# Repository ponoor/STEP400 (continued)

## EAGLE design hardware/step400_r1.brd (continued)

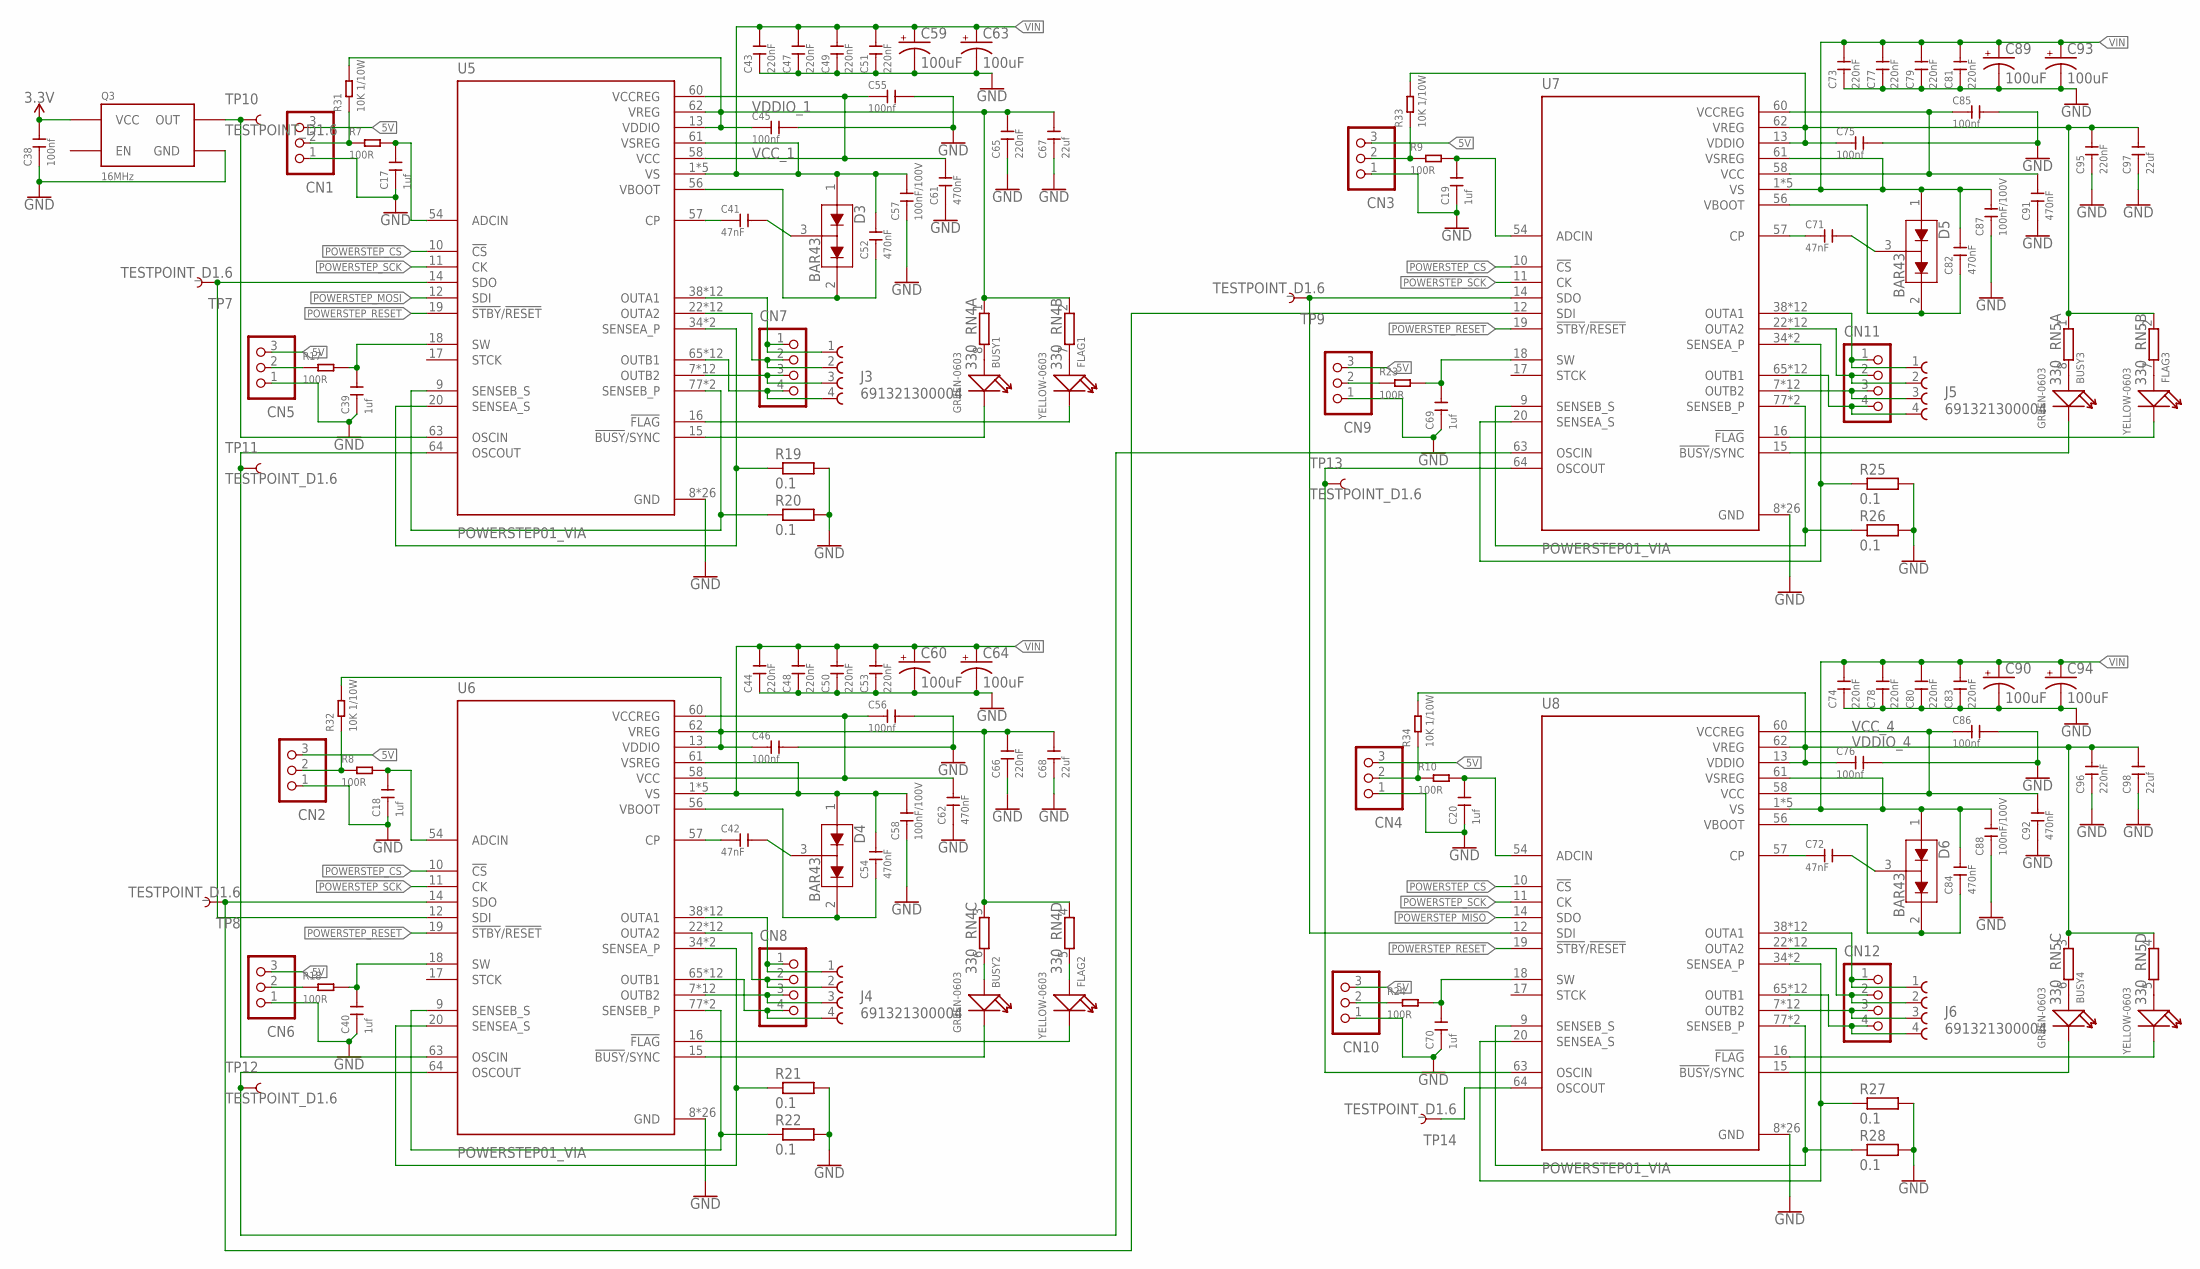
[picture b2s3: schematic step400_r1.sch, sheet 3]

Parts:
BUSY1, BUSY2, BUSY3, BUSY4: GREEN-0603; LED-0603
C17, C18, C19, C20, C39, C40, C69, C70: 1uf; C0603
C38, C45, C46, C55, C56, C75, C76, C85, C86: 100nf; C0402
C41, C42, C71, C72: 47nF; C0805
C43, C44, C47, C48, C49, C50, C51, C53, C73, C74, C77, C78, C79, C80, C81, C83: 220nF; C0805
C52, C54, C61, C62, C82, C84, C91, C92: 470nF; C0603
C57, C58, C87, C88: 100nF/100V; C0805
C59, C60, C63, C64, C89, C90, C93, C94: 100uF; E5-10,5
C65, C66, C95, C96: 220nF; C0402
C67, C68, C97, C98: 22uf; C0805
CN1, CN2, CN3, CN4, CN5, CN6, CN9, CN10: B3B-XASK-1
CN7, CN8, CN11, CN12: B4B-XASK-1
D3, D4, D5, D6: BAR43; SOT23-3
FLAG1, FLAG2, FLAG3, FLAG4: YELLOW-0603; LED-0603
J3, J4, J5, J6: 691321300004
Q3: 16MHz; SG5032
R7, R8, R9, R10, R17, R18, R23, R24: 100R; R0603
R19, R20, R21, R22, R25, R26, R27, R28: 0.1; RESC6332X71N
R31, R32, R33, R34: 10K 1/10W; R0603
RN4, RN5: 330; CAY16_LONG_W
TP7, TP8, TP9, TP10, TP11, TP12, TP13, TP14: TESTPOINT_D1.6
U5, U6, U7, U8: POWERSTEP01_VIA; IC_POWERSTEP01_VIA

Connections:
3.3V: C38.2, Q3.4 (VCC); also elsewhere on the board
5V: CN1.3, CN2.3, CN3.3, CN4.3, CN5.3, CN6.3, CN9.3, CN10.3; also elsewhere on the board
GND: C17.1, C18.1, C19.1, C20.1, C38.1, C39.1, C40.1, C43.1, C44.1, C45.2, C46.2, C47.1, C48.1, C49.1, C50.1, C51.1, C53.1, C55.2, C56.2, C57.1, C58.1, C59.-, C60.-, C61.1, C62.1, C63.-, C64.-, C65.1, C66.1, C67.1, C68.1, C69.1, C70.1, C73.1, C74.1, C75.2, C76.2, C77.1, C78.1, C79.1, C80.1, C81.1, C83.1, C85.2, C86.2, C87.1, C88.1, C89.-, C90.-, C91.1, C92.1, C93.-, C94.-, C95.1, C96.1, C97.1, C98.1, CN1.1, CN2.1, CN3.1, CN4.1, CN5.1, CN6.1, CN9.1, CN10.1, Q3.2 (GND), R19.2, R20.2, R21.2, R22.2, R25.2, R26.2, R27.2, R28.2, U5.8 (GND), U5.21 (GND), U5.59 (GND), U5.EPAD9 (GND), U5.EPAD9_VIA1 (GND), U5.EPAD9_VIA2 (GND), U5.EPAD9_VIA3 (GND), U5.EPAD9_VIA4 (GND), U5.EPAD9_VIA5 (GND), U5.EPAD9_VIA6 (GND), U5.EPAD9_VIA7 (GND), U5.EPAD9_VIA8 (GND), U5.EPAD9_VIA9 (GND), U5.EPAD9_VIA10 (GND), U5.EPAD9_VIA11 (GND), U5.EPAD9_VIA12 (GND), U5.EPAD9_VIA13 (GND), U5.EPAD9_VIA14 (GND), U5.EPAD9_VIA15 (GND), U5.EPAD9_VIA16 (GND), U5.EPAD9_VIA17 (GND), U5.EPAD9_VIA18 (GND), U5.EPAD9_VIA19 (GND), U5.EPAD9_VIA20 (GND), U5.EPAD9_VIA21 (GND), U5.EPAD9_VIA22 (GND), U6.8 (GND), U6.21 (GND), U6.59 (GND), U6.EPAD9 (GND), U6.EPAD9_VIA1 (GND), U6.EPAD9_VIA2 (GND), U6.EPAD9_VIA3 (GND), U6.EPAD9_VIA4 (GND), U6.EPAD9_VIA5 (GND), U6.EPAD9_VIA6 (GND), U6.EPAD9_VIA7 (GND), U6.EPAD9_VIA8 (GND), U6.EPAD9_VIA9 (GND), U6.EPAD9_VIA10 (GND), U6.EPAD9_VIA11 (GND), U6.EPAD9_VIA12 (GND), U6.EPAD9_VIA13 (GND), U6.EPAD9_VIA14 (GND), U6.EPAD9_VIA15 (GND), U6.EPAD9_VIA16 (GND), U6.EPAD9_VIA17 (GND), U6.EPAD9_VIA18 (GND), U6.EPAD9_VIA19 (GND), U6.EPAD9_VIA20 (GND), U6.EPAD9_VIA21 (GND), U6.EPAD9_VIA22 (GND), U7.8 (GND), U7.21 (GND), U7.59 (GND), U7.EPAD9 (GND), U7.EPAD9_VIA1 (GND), U7.EPAD9_VIA2 (GND), U7.EPAD9_VIA3 (GND), U7.EPAD9_VIA4 (GND), U7.EPAD9_VIA5 (GND), U7.EPAD9_VIA6 (GND), U7.EPAD9_VIA7 (GND), U7.EPAD9_VIA8 (GND), U7.EPAD9_VIA9 (GND), U7.EPAD9_VIA10 (GND), U7.EPAD9_VIA11 (GND), U7.EPAD9_VIA12 (GND), U7.EPAD9_VIA13 (GND), U7.EPAD9_VIA14 (GND), U7.EPAD9_VIA15 (GND), U7.EPAD9_VIA16 (GND), U7.EPAD9_VIA17 (GND), U7.EPAD9_VIA18 (GND), U7.EPAD9_VIA19 (GND), U7.EPAD9_VIA20 (GND), U7.EPAD9_VIA21 (GND), U7.EPAD9_VIA22 (GND), U8.8 (GND), U8.21 (GND), U8.59 (GND), U8.EPAD9 (GND), U8.EPAD9_VIA1 (GND), U8.EPAD9_VIA2 (GND), U8.EPAD9_VIA3 (GND), U8.EPAD9_VIA4 (GND), U8.EPAD9_VIA5 (GND), U8.EPAD9_VIA6 (GND), U8.EPAD9_VIA7 (GND), U8.EPAD9_VIA8 (GND), U8.EPAD9_VIA9 (GND), U8.EPAD9_VIA10 (GND), U8.EPAD9_VIA11 (GND), U8.EPAD9_VIA12 (GND), U8.EPAD9_VIA13 (GND), U8.EPAD9_VIA14 (GND), U8.EPAD9_VIA15 (GND), U8.EPAD9_VIA16 (GND), U8.EPAD9_VIA17 (GND), U8.EPAD9_VIA18 (GND), U8.EPAD9_VIA19 (GND), U8.EPAD9_VIA20 (GND), U8.EPAD9_VIA21 (GND), U8.EPAD9_VIA22 (GND); also elsewhere on the board
LIMIT1: C17.2, R7.2, U5.54 (ADCIN)
LIMIT2: C18.2, R8.2, U6.54 (ADCIN)
LIMIT3: C19.2, R9.2, U7.54 (ADCIN)
LIMIT4: C20.2, R10.2, U8.54 (ADCIN)
unnamed: TP14.1, U8.64 (OSCOUT)
unnamed: CN1.2, R7.1, R31.1
unnamed: CN2.2, R8.1, R32.1
unnamed: BUSY1.+, RN4.8 (2)
unnamed: CN5.2, R17.1
unnamed: C39.2, R17.2, U5.18 (SW)
unnamed: C40.2, R18.2, U6.18 (SW)
unnamed: CN6.2, R18.1
unnamed: C69.2, R23.2, U7.18 (SW)
unnamed: CN9.2, R23.1
unnamed: FLAG1.+, RN4.7 (2)
unnamed: C70.2, R24.2, U8.18 (SW)
unnamed: C41.2, D3.3 (COM)
unnamed: C41.1, U5.57 (CP)
unnamed: CN10.2, R24.1
unnamed: CN3.2, R9.1, R33.1
unnamed: BUSY2.+, RN4.6 (2)
unnamed: FLAG2.+, RN4.5 (2)
unnamed: FLAG1.-, U5.16 (!FLAG)
unnamed: BUSY1.-, U5.15 (!BUSY!/SYNC)
unnamed: R20.1, U5.9 (SENSEB_S), U5.77 (SENSEB_P), U5.82 (SENSEB_P)
unnamed: R19.1, U5.20 (SENSEA_S), U5.34 (SENSEA_P), U5.39 (SENSEA_P)
unnamed: CN4.2, R10.1, R34.1
unnamed: CN7.1, J3.1, U5.38 (OUTA1), U5.42 (OUTA1), U5.53 (OUTA1), U5.EPAD4 (OUTA1), U5.EPAD4_VIA1 (OUTA1), U5.EPAD4_VIA2 (OUTA1), U5.EPAD4_VIA3 (OUTA1), U5.EPAD4_VIA4 (OUTA1), U5.EPAD4_VIA5 (OUTA1), U5.EPAD4_VIA6 (OUTA1), U5.EPAD4_VIA7 (OUTA1), U5.EPAD4_VIA8 (OUTA1)
unnamed: CN7.2, J3.2, U5.22 (OUTA2), U5.33 (OUTA2), U5.37 (OUTA2), U5.EPAD3 (OUTA2), U5.EPAD3_VIA1 (OUTA2), U5.EPAD3_VIA2 (OUTA2), U5.EPAD3_VIA3 (OUTA2), U5.EPAD3_VIA4 (OUTA2), U5.EPAD3_VIA5 (OUTA2), U5.EPAD3_VIA6 (OUTA2), U5.EPAD3_VIA7 (OUTA2), U5.EPAD3_VIA8 (OUTA2)
unnamed: TP7.1, U5.14 (SDO), U6.12 (SDI)
unnamed: CN7.3, J3.3, U5.7 (OUTB2), U5.81 (OUTB2), U5.85 (OUTB2), U5.EPAD8 (OUTB2), U5.EPAD8_VIA1 (OUTB2), U5.EPAD8_VIA2 (OUTB2), U5.EPAD8_VIA3 (OUTB2), U5.EPAD8_VIA4 (OUTB2), U5.EPAD8_VIA5 (OUTB2), U5.EPAD8_VIA6 (OUTB2), U5.EPAD8_VIA7 (OUTB2), U5.EPAD8_VIA8 (OUTB2)
unnamed: CN7.4, J3.4, U5.65 (OUTB1), U5.76 (OUTB1), U5.80 (OUTB1), U5.EPAD7 (OUTB1), U5.EPAD7_VIA1 (OUTB1), U5.EPAD7_VIA2 (OUTB1), U5.EPAD7_VIA3 (OUTB1), U5.EPAD7_VIA4 (OUTB1), U5.EPAD7_VIA5 (OUTB1), U5.EPAD7_VIA6 (OUTB1), U5.EPAD7_VIA7 (OUTB1), U5.EPAD7_VIA8 (OUTB1)
unnamed: C42.2, D4.3 (COM)
unnamed: C42.1, U6.57 (CP)
unnamed: BUSY3.+, RN5.8 (2)
unnamed: FLAG3.+, RN5.7 (2)
unnamed: FLAG2.-, U6.16 (!FLAG)
unnamed: BUSY2.-, U6.15 (!BUSY!/SYNC)
unnamed: R22.1, U6.9 (SENSEB_S), U6.77 (SENSEB_P), U6.82 (SENSEB_P)
unnamed: R21.1, U6.20 (SENSEA_S), U6.34 (SENSEA_P), U6.39 (SENSEA_P)
unnamed: TP12.1, U6.64 (OSCOUT), U7.63 (OSCIN)
unnamed: CN8.1, J4.1, U6.38 (OUTA1), U6.42 (OUTA1), U6.53 (OUTA1), U6.EPAD4 (OUTA1), U6.EPAD4_VIA1 (OUTA1), U6.EPAD4_VIA2 (OUTA1), U6.EPAD4_VIA3 (OUTA1), U6.EPAD4_VIA4 (OUTA1), U6.EPAD4_VIA5 (OUTA1), U6.EPAD4_VIA6 (OUTA1), U6.EPAD4_VIA7 (OUTA1), U6.EPAD4_VIA8 (OUTA1)
unnamed: CN8.2, J4.2, U6.22 (OUTA2), U6.33 (OUTA2), U6.37 (OUTA2), U6.EPAD3 (OUTA2), U6.EPAD3_VIA1 (OUTA2), U6.EPAD3_VIA2 (OUTA2), U6.EPAD3_VIA3 (OUTA2), U6.EPAD3_VIA4 (OUTA2), U6.EPAD3_VIA5 (OUTA2), U6.EPAD3_VIA6 (OUTA2), U6.EPAD3_VIA7 (OUTA2), U6.EPAD3_VIA8 (OUTA2)
unnamed: CN8.3, J4.3, U6.7 (OUTB2), U6.81 (OUTB2), U6.85 (OUTB2), U6.EPAD8 (OUTB2), U6.EPAD8_VIA1 (OUTB2), U6.EPAD8_VIA2 (OUTB2), U6.EPAD8_VIA3 (OUTB2), U6.EPAD8_VIA4 (OUTB2), U6.EPAD8_VIA5 (OUTB2), U6.EPAD8_VIA6 (OUTB2), U6.EPAD8_VIA7 (OUTB2), U6.EPAD8_VIA8 (OUTB2)
unnamed: CN8.4, J4.4, U6.65 (OUTB1), U6.76 (OUTB1), U6.80 (OUTB1), U6.EPAD7 (OUTB1), U6.EPAD7_VIA1 (OUTB1), U6.EPAD7_VIA2 (OUTB1), U6.EPAD7_VIA3 (OUTB1), U6.EPAD7_VIA4 (OUTB1), U6.EPAD7_VIA5 (OUTB1), U6.EPAD7_VIA6 (OUTB1), U6.EPAD7_VIA7 (OUTB1), U6.EPAD7_VIA8 (OUTB1)
unnamed: BUSY4.+, RN5.6 (2)
unnamed: C82.1, D5.2 (C2), U7.56 (VBOOT)
unnamed: C71.2, D5.3 (COM)
unnamed: C71.1, U7.57 (CP)
unnamed: FLAG4.+, RN5.5 (2)
unnamed: CN11.4, J5.4, U7.65 (OUTB1), U7.76 (OUTB1), U7.80 (OUTB1), U7.EPAD7 (OUTB1), U7.EPAD7_VIA1 (OUTB1), U7.EPAD7_VIA2 (OUTB1), U7.EPAD7_VIA3 (OUTB1), U7.EPAD7_VIA4 (OUTB1), U7.EPAD7_VIA5 (OUTB1), U7.EPAD7_VIA6 (OUTB1), U7.EPAD7_VIA7 (OUTB1), U7.EPAD7_VIA8 (OUTB1)
unnamed: FLAG3.-, U7.16 (!FLAG)
unnamed: BUSY3.-, U7.15 (!BUSY!/SYNC)
unnamed: R26.1, U7.9 (SENSEB_S), U7.77 (SENSEB_P), U7.82 (SENSEB_P)
unnamed: R25.1, U7.20 (SENSEA_S), U7.34 (SENSEA_P), U7.39 (SENSEA_P)
unnamed: TP8.1, U6.14 (SDO), U7.12 (SDI)
unnamed: CN11.1, J5.1, U7.38 (OUTA1), U7.42 (OUTA1), U7.53 (OUTA1), U7.EPAD4 (OUTA1), U7.EPAD4_VIA1 (OUTA1), U7.EPAD4_VIA2 (OUTA1), U7.EPAD4_VIA3 (OUTA1), U7.EPAD4_VIA4 (OUTA1), U7.EPAD4_VIA5 (OUTA1), U7.EPAD4_VIA6 (OUTA1), U7.EPAD4_VIA7 (OUTA1), U7.EPAD4_VIA8 (OUTA1)
unnamed: CN11.2, J5.2, U7.22 (OUTA2), U7.33 (OUTA2), U7.37 (OUTA2), U7.EPAD3 (OUTA2), U7.EPAD3_VIA1 (OUTA2), U7.EPAD3_VIA2 (OUTA2), U7.EPAD3_VIA3 (OUTA2), U7.EPAD3_VIA4 (OUTA2), U7.EPAD3_VIA5 (OUTA2), U7.EPAD3_VIA6 (OUTA2), U7.EPAD3_VIA7 (OUTA2), U7.EPAD3_VIA8 (OUTA2)
unnamed: CN11.3, J5.3, U7.7 (OUTB2), U7.81 (OUTB2), U7.85 (OUTB2), U7.EPAD8 (OUTB2), U7.EPAD8_VIA1 (OUTB2), U7.EPAD8_VIA2 (OUTB2), U7.EPAD8_VIA3 (OUTB2), U7.EPAD8_VIA4 (OUTB2), U7.EPAD8_VIA5 (OUTB2), U7.EPAD8_VIA6 (OUTB2), U7.EPAD8_VIA7 (OUTB2), U7.EPAD8_VIA8 (OUTB2)
unnamed: CN12.4, J6.4, U8.65 (OUTB1), U8.76 (OUTB1), U8.80 (OUTB1), U8.EPAD7 (OUTB1), U8.EPAD7_VIA1 (OUTB1), U8.EPAD7_VIA2 (OUTB1), U8.EPAD7_VIA3 (OUTB1), U8.EPAD7_VIA4 (OUTB1), U8.EPAD7_VIA5 (OUTB1), U8.EPAD7_VIA6 (OUTB1), U8.EPAD7_VIA7 (OUTB1), U8.EPAD7_VIA8 (OUTB1)
unnamed: CN12.3, J6.3, U8.7 (OUTB2), U8.81 (OUTB2), U8.85 (OUTB2), U8.EPAD8 (OUTB2), U8.EPAD8_VIA1 (OUTB2), U8.EPAD8_VIA2 (OUTB2), U8.EPAD8_VIA3 (OUTB2), U8.EPAD8_VIA4 (OUTB2), U8.EPAD8_VIA5 (OUTB2), U8.EPAD8_VIA6 (OUTB2), U8.EPAD8_VIA7 (OUTB2), U8.EPAD8_VIA8 (OUTB2)
unnamed: C84.1, D6.2 (C2), U8.56 (VBOOT)
unnamed: C72.2, D6.3 (COM)
unnamed: C72.1, U8.57 (CP)
unnamed: FLAG4.-, U8.16 (!FLAG)
unnamed: BUSY4.-, U8.15 (!BUSY!/SYNC)
unnamed: R28.1, U8.9 (SENSEB_S), U8.77 (SENSEB_P), U8.82 (SENSEB_P)
unnamed: R27.1, U8.20 (SENSEA_S), U8.34 (SENSEA_P), U8.39 (SENSEA_P)
unnamed: CN12.1, J6.1, U8.38 (OUTA1), U8.42 (OUTA1), U8.53 (OUTA1), U8.EPAD4 (OUTA1), U8.EPAD4_VIA1 (OUTA1), U8.EPAD4_VIA2 (OUTA1), U8.EPAD4_VIA3 (OUTA1), U8.EPAD4_VIA4 (OUTA1), U8.EPAD4_VIA5 (OUTA1), U8.EPAD4_VIA6 (OUTA1), U8.EPAD4_VIA7 (OUTA1), U8.EPAD4_VIA8 (OUTA1)
unnamed: CN12.2, J6.2, U8.22 (OUTA2), U8.33 (OUTA2), U8.37 (OUTA2), U8.EPAD3 (OUTA2), U8.EPAD3_VIA1 (OUTA2), U8.EPAD3_VIA2 (OUTA2), U8.EPAD3_VIA3 (OUTA2), U8.EPAD3_VIA4 (OUTA2), U8.EPAD3_VIA5 (OUTA2), U8.EPAD3_VIA6 (OUTA2), U8.EPAD3_VIA7 (OUTA2), U8.EPAD3_VIA8 (OUTA2)
unnamed: Q3.3 (OUT), TP10.1, U5.63 (OSCIN)
unnamed: TP11.1, U5.64 (OSCOUT), U6.63 (OSCIN)
unnamed: TP13.1, U7.64 (OSCOUT), U8.63 (OSCIN)
unnamed: TP9.1, U7.14 (SDO), U8.12 (SDI)
POWERSTEP_CS: U5.10 (!CS), U6.10 (!CS), U7.10 (!CS), U8.10 (!CS); also elsewhere on the board
POWERSTEP_MISO: U8.14 (SDO); also elsewhere on the board
POWERSTEP_MOSI: U5.12 (SDI); also elsewhere on the board
POWERSTEP_RESET: U5.19 (!STBY!/!RESET), U6.19 (!STBY!/!RESET), U7.19 (!STBY!/!RESET), U8.19 (!STBY!/!RESET); also elsewhere on the board
POWERSTEP_SCK: U5.11 (CK), U6.11 (CK), U7.11 (CK), U8.11 (CK); also elsewhere on the board
VBOOT_1: C52.1, D3.2 (C2), U5.56 (VBOOT)
VBOOT_2: C54.1, D4.2 (C2), U6.56 (VBOOT)
VCC_1: C55.1, C61.2, U5.58 (VCC), U5.60 (VCCREG)
VCC_2: C56.1, C62.2, U6.58 (VCC), U6.60 (VCCREG)
VCC_3: C85.1, C91.2, U7.58 (VCC), U7.60 (VCCREG)
VCC_4: C86.1, C92.2, U8.58 (VCC), U8.60 (VCCREG)
VDDIO_1: C45.1, C65.2, C67.2, R31.2, RN4.1, RN4.2 (1), U5.13 (VDDIO), U5.62 (VREG)
VDDIO_2: C46.1, C66.2, C68.2, R32.2, RN4.3 (1), RN4.4 (1), U6.13 (VDDIO), U6.62 (VREG)
VDDIO_3: C75.1, C95.2, C97.2, R33.2, RN5.1, RN5.2 (1), U7.13 (VDDIO), U7.62 (VREG)
VDDIO_4: C76.1, C96.2, C98.2, R34.2, RN5.3 (1), RN5.4 (1), U8.13 (VDDIO), U8.62 (VREG)
VIN: C43.2, C44.2, C47.2, C48.2, C49.2, C50.2, C51.2, C52.2, C53.2, C54.2, C57.2, C58.2, C59.+, C60.+, C63.+, C64.+, C73.2, C74.2, C77.2, C78.2, C79.2, C80.2, C81.2, C82.2, C83.2, C84.2, C87.2, C88.2, C89.+, C90.+, C93.+, C94.+, D3.1 (A1), D4.1 (A1), D5.1 (A1), D6.1 (A1), U5.1 (VS), U5.23 (VS), U5.43 (VS), U5.55 (VS), U5.61 (VSREG), U5.66 (VS), U6.1 (VS), U6.23 (VS), U6.43 (VS), U6.55 (VS), U6.61 (VSREG), U6.66 (VS), U7.1 (VS), U7.23 (VS), U7.43 (VS), U7.55 (VS), U7.61 (VSREG), U7.66 (VS), U8.1 (VS), U8.23 (VS), U8.43 (VS), U8.55 (VS), U8.61 (VSREG), U8.66 (VS); also elsewhere on the board

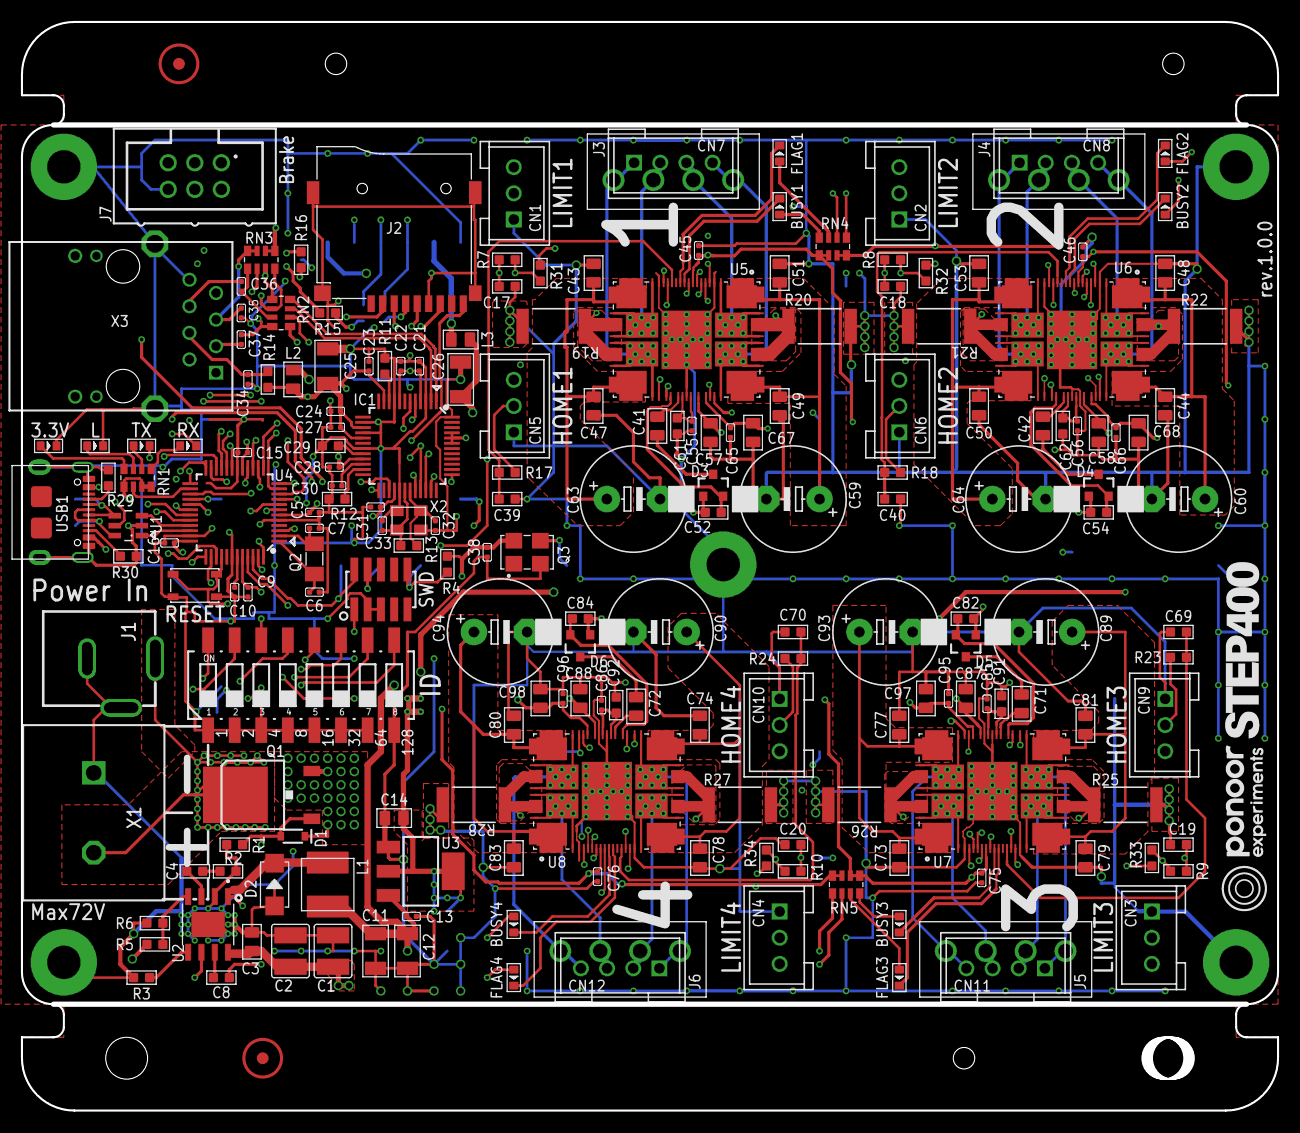
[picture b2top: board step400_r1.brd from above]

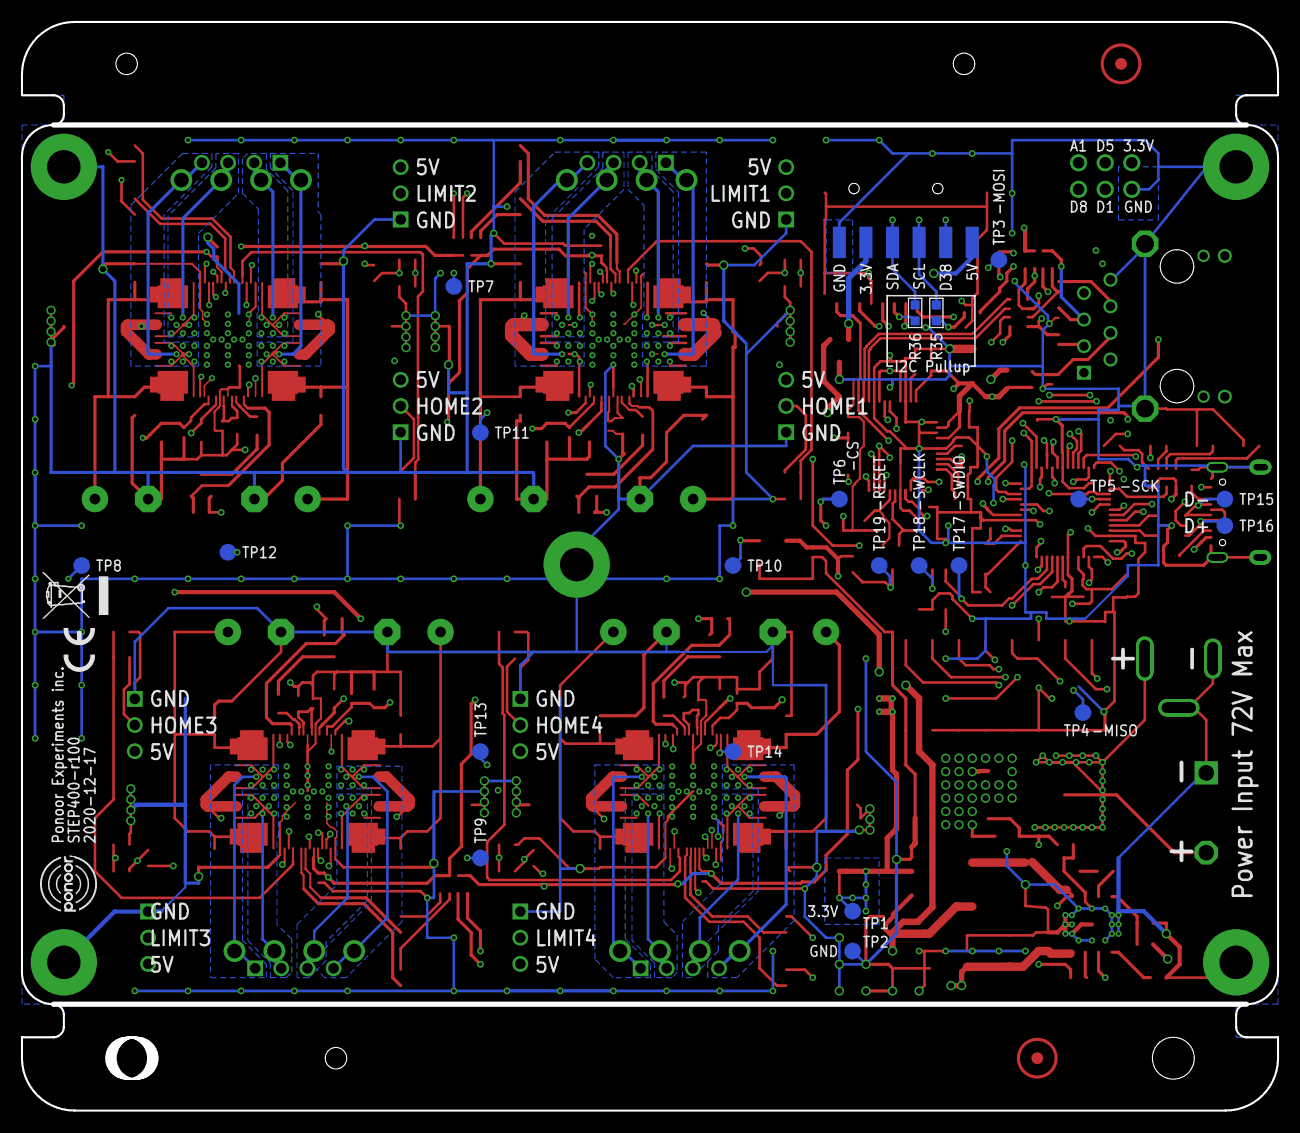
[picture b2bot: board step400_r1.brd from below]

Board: 4 copper layers, 120.0 x 104.0 mm, 229 parts (25 on the bottom side), 166 nets.

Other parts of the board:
U$1: STEP400_LOGO_6MM
U$2, U$3: FIDUCIAL_MARKER_PBAN
U$4: PONOOR_LOGO_6MM
U$6: WEEE_6MM
U$8: CE_3MM

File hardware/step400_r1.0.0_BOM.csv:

#,Name,Value,Description,Package,Manufacture,Manufacturer Part Number,Designator,Qty,Type,
1,SMD-LED,GREEN,general LED green,LED-0603,Lite-On,LTST-C193TGKT-5A,"3.3V, BUSY1, BUSY2, BUSY3, BUSY4",5,SMD,
2,MLCC,4.7uF/100V,4.7uF / 20% / 100V / X5R,C1210,Samsung Electro-Mechanics,CL32B475KCVZW6E,"C1, C2",2,SMD,
3,MLCC,47uF/6.3V,47uF / 20% / 6.3V / X5R,C1206,Samsung Electro-Mechanics,CL31A476MQHNNWE,"C11, C12, C25, C26",4,SMD,
4,MLCC,10uF/10V,10uF / 20% / 10V / X5R,C0805,Samsung Electro-Mechanics,CL21A106KOQNNNG,C14,1,SMD,
5,MLCC,1uF/6.3V,1uF / 20% / 6.3V / X5R,C0603,Samsung Electro-Mechanics,CL10A105KO8NNNC,"C17, C18, C19, C20, C39, C40, C69, C70",8,SMD,
6,MLCC,4.7uF/6.3V,4.7uF / 20% / 6.3V / X5R,C0603,Samsung Electro-Mechanics,CL10A475KQ8NNNC,C29,1,SMD,
7,MLCC,100nF/100V,100nF / 20% / 100V / X5R,C0805,Samsung Electro-Mechanics,CL21B104KCFNNNE,"C3, C57, C58, C87, C88",5,SMD,
8,MLCC,10nF/25V,10nF / 20% / 25V / X5R ,C0402,Walsin Tech Corp,0402B103K250,"C30, C35",2,SMD,
9,MLCC,22nF 50V,22nF / 20% / 50V / X5R,C0402,Walsin Tech Corp,0402F223Z500CT,C34,1,SMD,
10,MLCC,6.8nF/25V,6.8nF / 20% / 25V / X5R ,C0402,Walsin Tech Corp,0402B682K500CT,"C36, C37",2,SMD,
11,MLCC,100nF/50V,100nF / 20% / 50V / X5R,C0603,Walsin Tech Corp,0603B104K500CT,"C4, C8",2,SMD,
12,MLCC,47nF/50V,47nF / 20% / 50V / X5R,C0805,Samsung Electro-Mechanics,CL21F473ZBANNNC,"C41, C42, C71, C72",4,SMD,
13,MLCC,220nF/100V,220nF / 20% / 100V / X5R,C0805,Samsung Electro-Mechanics,CL21B224KCFSFNE,"C43, C44, C47, C48, C49, C50, C51, C53, C73, C74, C77, C78, C79, C80, C81, C83",16,SMD,
14,MLCC,100nF / 25V,100nF / 20% / 25V / X5R,C0402,Walsin Tech Corp,0402X104K160CT,"C5, C9, C10, C13, C15, C16, C21, C22, C23, C24, C27, C28, C31, C38, C45, C46, C55, C56, C75, C76, C85, C86",22,SMD,
15,MLCC,470nF/25V,470nF / 20% / 25V / X5R ,C0603,Samsung Electro-Mechanics,CL10B474KA8NNNC,"C52, C54, C61, C62, C82, C84, C91, C92",8,SMD,
16,Chemical Capacitor,100uF/100V,100uF / 20% / 100V,"E5-10,5",Rubycon,100PX100MEFC10X16,"C59, C60, C63, C64, C89, C90, C93, C94",8,THT,
17,MLCC,22pF/50V,22pF / 10% / 50V / X5R,C0402,Walsin Tech Corp,0402N220J500,"C6, C7, C32, C33",4,SMD,
18,MLCC,220nF/6.3V,220nF / 20% / 6.3V / X5R,C0402,Walsin Tech Corp,0402X224K6R3CT,"C65, C66, C95, C96",4,SMD,
19,MLCC,22uF/6.3V,22uF / 20% / 6.3V / X5R,C0805,Samsung Electro-Mechanics,CL21A226MQQNNNE,"C67, C68, C97, C98",4,SMD,
20,Shrouded header,"2.5mm, 3P",B3B-XASK-1,B3B-XASK-1,JST,B03B-XASK-1(LF)(SN),"CN1, CN2, CN3, CN4, CN5, CN6, CN9, CN10",8,THT,
21,Shrouded header,"2.5mm, 4P",B4B-XASK-1,B4B-XASK-1,JST,B04B-XASK-1(LF)(SN),"CN7, CN8, CN11, CN12",4,THT,NO mount
22,Zener Diode,"5.6V, 300mW",5.6V ±7% 300mW ,SOD-323,ON Semiconductor,MM3Z5V6T1G,D1,1,SMD,
23,Schottky diode,100V 2A,"100V, 2A",DO-214AC,Guangdong Hottech,SS210A,D2,1,SMD,
24,Switching diode array,BAR43,"30V, 100mA",SOT23-3,STMicroelectronics,BAR43SFILM,"D3, D4, D5, D6",4,SMD,
25,SMD-LED,Red,general LED red,LED-0603,Lite-On,LTST-C193KRKT-5A,"FLAG1, FLAG2, FLAG3, FLAG4, TX",5,SMD,
26,Ethernet Controller,,,TQFP48,WIZnet,W5500,IC1,1,SMD,
27,DIP Switch,,8 digits,2.54mm pitch SMD,Cixi Tonver Elec,HAD-08HWA-R,ID,1,SMD,
28,DC Power receptacle,,DC Power Receptacle Jack 5A 2.0mm 6.2mm,POWERJACK_SLOT,XKB Connectivity,DC-005-5A-2.0,J1,1,SMD,
29,Micro SD card slot,,,,XUNPU,TF-115K,J2,1,SMD,
30,3.81mm 4pin header,,,,Ningbo Kangnex Elec,WJ15EDGVC-3.81-4P,"J3, J4, J5, J6",4,THT,
31,Box header,,"Header 6P 0.100""(2.54mm) 2",61200621621,Ckmtw(Shenzhen Cankemeng),C132438,J7,1,THT,
32,SMD-LED,Orange,general LED orange,LED-0603,Lite-On,LTST-C191KFKT,L,1,SMD,
33,Power Inductor,15uH,±20% 1.9A,L5050,TDK,VLS5045EX-150M,L1,1,SMD,
34,Ferrite Beads,330R-1500MA,330Ω @ 100MHz 1.5A,L0805,Murata Electronics,"BLM21PG331SN1D","L2, L3",2,SMD,
35,P-MOSFET,,100V 46A,D-PAK(TO252AA),Winsok Semicon,WSF45P10,Q1,1,SMD,
36,Crystal Resonators,32.768kHz,CRYSTAL,SMD-3215_2P,EPSON,FC-135 32.7680KA-A0,Q2,1,SMD,
37,Crystal Oscillator,,16MHz ±100ppm 3.3V,SG5032,Seiko Epson,X1G004451000200,Q3,1,SMD,
38,Chip Resistor,100k,5% 1/10W,R0603,YAGEO,RC0603JR-07100KL,R1,1,SMD,
39,Chip Resistor,12.4K,1％ 1/10W,R0603,YAGEO,AC0603FR-0712K4L,R11,1,SMD,
40,Chip Resistor,1M 1/10W,5% 1/10W,R0603,YAGEO,AC0603JR-071ML,R13,1,SMD,
41,Chip Resistor,10R,5% 1/10W,R0603,YAGEO,RC0603JR-0710RL,R14,1,SMD,
42,Chip Resistor,330R,5% 1/10W,R0603,YAGEO,RC0603JR-07330RL,"R15, R16",2,SMD,
43,Chip Resistor,0.1,1% 3W,R2512,Bourns,CRA2512-FZ-R100ELF,"R19, R20, R21, R22, R25, R26, R27, R28",8,SMD,
44,Chip Resistor,4.7k,5% 1/10W,R0603,YAGEO,AC0603JR-074K7L,R2,1,SMD,
45,Chip Resistor,5.1k,±0.5% 0.1W,R0603,YAGEO,RC0603DR-075K1L,"R29, R30",2,SMD,
46,Chip Resistor,13k,1％ 1/10W,R0603,YAGEO,RC0603FR-0713KL,R3,1,SMD,
47,Chip Resistor,10K 1/10W,5% 1/10W,R0603,YAGEO,RC0603JR-0710KL,"R4, R12, R31, R32, R33, R34",6,SMD,
48,Chip Resistor,3k,1％ 1/10W,R0603,YAGEO,RC0603FR-073KL,R5,1,SMD,
49,Chip Resistor,750,1％ 1/10W,R0603,YAGEO,AC0603DR-07750RL,R6,1,SMD,
50,Chip Resistor,100R,5% 1/10W,R0603,YAGEO,RC0603JR-07100RL,"R7, R8, R9, R10, R17, R18, R23, R24",8,SMD,
51,Tactile Switch,,SWITCH-SPST,4.6x3.2,ALPS Electric,SKRPABE010,RESET,1,SMD,
52,Array Chip Resistor,330,5% 1/16W,R0603 x4,Bourns,CAY16-331J4LF,"RN1, RN4, RN5",3,SMD,
53,Array Chip Resistor,33,5% 1/16W,R0603 x4,Bourns,CAY16-330J4LF,RN2,1,SMD,
54,Array Chip Resistor,49.9,1% 1/16W,R0603 x4,Bourns,CAY16-49R9F4LF,RN3,1,SMD,
55,SMD-LED,Yellow,general LED yellow,LED-0603,Lite-On,LTST-C191KSKT,RX,1,SMD,
56,Pin Header,10 pin,Cortex Debug Connector,1.27mm Pin Header 10P,Amphenol ICC,20021121-00010C4LF,SWD,1,SMD,
57,TVS Diode Array,USBLC6-2SC6,STMicroelectronics  USBLC6,SOT23-6L,STMicroelectronics,USBLC6-2SC6,U1,1,SMD,
58,DC-DC converter,,,HTSOP-J8,ROHM,BD9G341AEFJ-E2,U2,1,SMD,
59,Voltage Regulator,LD1117S33,3.3V 0.8A,SOT223,STMicroelectronics,LD1117S33TR,U3,1,SMD,
60,MCU,,,TQFP-48,Microchip,ATSAMD21G18A-AU,U4,1,SMD,
61,Stepper Motor Driver,,,VFQFPN89,STMicroelectronics,POWERSTEP01TR,"U5, U6, U7, U8",4,SMD,
62,USB Type C Connector,,USB - Type C Female 16 SMT,USB-C_USB2.0-TYPE-C,XKB Connectivity,U262-161N-4BVC11,USB1,1,THT,
63,Barrier Terminal Block,"7.62mm, 2P",,7.62mm,Ningbo Kangnex Elec,WJ25C-B-7.62-2P,X1,1,SMD,
64,Crystal Resonators ,25MHz,25MHz ±20ppm12pF,CRYSTAL-3225,Seiko Epson,X1E000021013900,X2,1,SMD,
65,RJ45 Jack with Magnetics,,,,Hanrun,HR871181A,X3,1,THT,

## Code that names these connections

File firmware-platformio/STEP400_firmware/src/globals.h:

// globals.h

#ifndef _GLOBALS_h
#define _GLOBALS_h

#if defined(ARDUINO) && ARDUINO >= 100
	#include "arduino.h"
#else
	#include "WProgram.h"
#endif
#include <SPI.h>
#include <Ponoor_PowerSTEP01Library.h>
#include <Ethernet.h>

//#define PROTOTYPE_R4 // Uncomment this line for the prototype r4 pcb.

// =============================================================================
// Pin definitions
// =============================================================================
#define ledPin	13u

#ifdef PROTOTYPE_R4
const uint8_t dipSwPin[8] = { A5,SCL,7u,SDA,2u,9u,3u,0u }; // Prototype_r4
const uint8_t limitSwPin[4] = { 1u,5u,8u,A1 };
#else
const uint8_t dipSwPin[8] = { 7u,30u,A5,31u,2u,9u,3u,0u };
#endif

#define SD_CS_PIN	4u

const uint8_t brakePin[4] = { A1,8u,5u,1u };
#define SD_DETECT_PIN   A4

#define POWERSTEP_MISO	6u	// D6 /SERCOM3/PAD[2] miso
#define POWERSTEP_MOSI	11u	// D11/SERCOM3/PAD[0] mosi
#define POWERSTEP_SCK	12u	// D12/SERCOM3/PAD[3] sck
#define POWERSTEP_CS_PIN A0
#define POWERSTEP_RESET_PIN A2

#define W5500_RESET_PIN A3

// =============================================================================
// Constants and variables
// =============================================================================

// General
#define COMPILE_DATE __DATE__
#define COMPILE_TIME __TIME__
extern const char *firmwareName;
extern const uint8_t firmwareVersion[3]; // defined in the main Arduino sketch
extern int8_t loadedConfigVersion[2];
extern const uint8_t applicableConfigVersion[2];
#define STATUS_POLL_PERIOD   1 // [ms]


// Tx, Rx LED
extern bool rxLedEnabled, txLedEnabled;
extern uint32_t RXL_blinkStartTime, TXL_blinkStartTime;
#define RXL_TXL_BLINK_DURATION	30 // ms

// Json configuration file
constexpr char* filename = "/config.txt";
extern String configName;
extern String configTargetProduct;
extern bool sdInitializeSucceeded;
extern bool configFileOpenSucceeded;
extern bool configFileParseSucceeded;

// PowerSTEP01
#define NUM_OF_MOTOR   (4)
extern powerSTEP stepper[];
#define MOTOR_ID_ALL    255
#define MOTOR_ID_FIRST  1
#define MOTOR_ID_LAST   4

// Network
extern uint8_t mac[6], mac_from_config[6], myId;
extern IPAddress
    myIp,
    myIp_from_config,
    destIp,
    dns,
    gateway,
    subnet;
const IPAddress broadcastIp(255, 255, 255, 255);
extern unsigned int inPort, outPort, outPort_from_config;
extern EthernetUDP Udp;
extern bool
    isDestIpSet,
    isMyIpAddId,
    isMacAddId,
    isOutPortAddId,
    bootedMsgEnable,
    isWaitingSendBootMsg,
    reportErrors;
#define BOOT_MSG_WAIT_TIME  1000    //[ms], The waiting duration for sending a boot message after Ethernet has been linked

// Motor settings.
#define TVAL_LIMIT_VAL  64 // approx. 5A

// Brake
extern uint8_t brakeStatus[NUM_OF_MOTOR];
enum {
    BRAKE_ENGAGED = 0,
    BRAKE_DISENGAGE_WAITING, // motor excited
    BRAKE_DISENGAGED,
    BRAKE_MOTORHIZ_WAITING // brake closed
};
extern uint32_t brakeTransitionTrigTime[NUM_OF_MOTOR];
extern bool bBrakeDecWaiting[NUM_OF_MOTOR]; // Waiting deceleration for the brake engaging procedure

// Homing
extern uint32_t homingStartTime[NUM_OF_MOTOR];
extern uint8_t homingStatus[NUM_OF_MOTOR];
extern bool bHoming[NUM_OF_MOTOR];
extern float homingSpeed[NUM_OF_MOTOR];
enum {
    HOMING_UNDEFINED = 0,
    HOMING_GOUNTIL,
    HOMING_RELEASESW,
    HOMING_COMPLETED,
    HOMING_TIMEOUT
};

// Command errors
enum {
    ERROR_COMMAND_IGNORED = 0,
    ERROR_MOTORID_NOTMATCH,
    ERROR_BRAKE_ENGAGED,
    ERROR_HOMESW_ACTIVATING,
    ERROR_LIMITSW_ACTIVATING,
    ERROR_GOUNTIL_TIMEOUT,
    ERROR_RELEASESW_TIMEOUT,
    ERROR_IN_SERVO_MODE
};
const String commandErrorText[8] = {
    F("CommandIgnored"),
    F("MotorIdNotMatch"),
    F("BrakeEngaged"),
    F("HomeSwActivating"),
    F("LimitSwActivating"),
    F("GoUntilTimeout"),
    F("ReleaseSwTimeout"),
    F("InServoMode")
};
// These values will be initialized at loadConfig()
extern bool
    busy[NUM_OF_MOTOR],
    HiZ[NUM_OF_MOTOR],
    homeSwState[NUM_OF_MOTOR],
    dir[NUM_OF_MOTOR],
    uvloStatus[NUM_OF_MOTOR];
extern uint8_t
    motorStatus[NUM_OF_MOTOR],
    thermalStatus[NUM_OF_MOTOR];

extern bool
    reportBUSY[NUM_OF_MOTOR],
    reportHiZ[NUM_OF_MOTOR],
    reportHomeSwStatus[NUM_OF_MOTOR],
    reportDir[NUM_OF_MOTOR],
    reportMotorStatus[NUM_OF_MOTOR],
    reportSwEvn[NUM_OF_MOTOR],
    reportUVLO[NUM_OF_MOTOR],
    reportThermalStatus[NUM_OF_MOTOR],
    reportOCD[NUM_OF_MOTOR],
    reportStall[NUM_OF_MOTOR],
    limitSwState[NUM_OF_MOTOR],
    reportLimitSwStatus[NUM_OF_MOTOR],
    limitSwMode[NUM_OF_MOTOR],
    homingDirection[NUM_OF_MOTOR],
    bProhibitMotionOnHomeSw[NUM_OF_MOTOR],
    bProhibitMotionOnLimitSw[NUM_OF_MOTOR],
    bHomingAtStartup[NUM_OF_MOTOR];
extern uint16_t
    goUntilTimeout[NUM_OF_MOTOR],
    releaseSwTimeout[NUM_OF_MOTOR];
extern uint8_t kvalHold[NUM_OF_MOTOR], kvalRun[NUM_OF_MOTOR], kvalAcc[NUM_OF_MOTOR], kvalDec[NUM_OF_MOTOR];
extern uint8_t tvalHold[NUM_OF_MOTOR], tvalRun[NUM_OF_MOTOR], tvalAcc[NUM_OF_MOTOR], tvalDec[NUM_OF_MOTOR];
extern bool isCurrentMode[NUM_OF_MOTOR];
extern bool homeSwMode[NUM_OF_MOTOR];

extern uint16_t intersectSpeed[NUM_OF_MOTOR]; // INT_SPEED
extern uint8_t
    startSlope[NUM_OF_MOTOR], // ST_SLP
    accFinalSlope[NUM_OF_MOTOR], // FN_SLP_ACC
    decFinalSlope[NUM_OF_MOTOR], // FN_SLP_DEC
    stallThreshold[NUM_OF_MOTOR]; // STALL_TH
extern uint8_t
    fastDecaySetting[NUM_OF_MOTOR], // T_FAST
    minOnTime[NUM_OF_MOTOR], // TON_MIN
    minOffTime[NUM_OF_MOTOR]; // TOFF_MIN
extern uint8_t
    overCurrentThreshold[NUM_OF_MOTOR], // OCD
    microStepMode[NUM_OF_MOTOR]; // STEP_MODE
extern uint16_t slewRate[NUM_OF_MOTOR]; // GATECFG1
extern uint8_t slewRateNum[NUM_OF_MOTOR]; // [0]114, [1]220, [2]400, [3]520, [4]790, [5]980.
extern float lowSpeedOptimize[NUM_OF_MOTOR];
extern bool electromagnetBrakeEnable[NUM_OF_MOTOR];
extern uint16_t brakeTransitionDuration[NUM_OF_MOTOR];
extern float
    acc[NUM_OF_MOTOR],
    dec[NUM_OF_MOTOR],
    maxSpeed[NUM_OF_MOTOR],
    fullStepSpeed[NUM_OF_MOTOR];

// Servo mode
extern int32_t targetPosition[NUM_OF_MOTOR];
extern float kP[NUM_OF_MOTOR], kI[NUM_OF_MOTOR], kD[NUM_OF_MOTOR];
extern boolean isServoMode[NUM_OF_MOTOR];
#endif

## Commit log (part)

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2020-12-18 Added hardware design files.
2020-12-18 updated .gitignore
2020-12-20 Added BOM lists
2021-01-23 Added a hardware inspection sketch
2021-01-25 Added config tool files
2021-01-26 Convert multiple .ino files style to .h .cpp style
2021-01-27 Added the PlatformIO working folder
2021-02-15 update osc float/int compatibility for each commands
2021-02-17 electromagnet brake update
2021-02-18 update config tool
2021-02-25 homing functions
2021-02-26 Homing updates
2021-02-26 added new items to the configTool index.html
2021-02-26 updated main.js in configTools
2021-02-26 updated new config items
2021-03-01 update config and error
2021-03-01 MAC address update
2021-03-02 updates for diagnosis
2021-03-03 Added inServboMode error
2021-03-03 Update Arduino sketch folder
2021-03-03 Added schematics PDFs
2021-03-05 added /getHiZ
2021-03-09 Added prototype version PCB support
2021-03-09 Arduino sketch folder update
2021-03-12 Fixed setTval bug
2021-03-12 Fixed a bug at setTval
2021-03-14 configTool updates
2021-03-15 error message updates
2021-03-24 Added config json files
2021-03-24 config value fixed
2021-03-24 Added config files
2021-03-25 Added new config examples
2021-03-25 Added 23HS5628 configs
2021-04-10 Fixed a problem of starting up with a current mode.
    Fixed a problem that a request to start in a current drive mode in the configTool is ignored.
    Also fixed some typos.
2021-04-15 Fixed driving mode setups at a startup.
2021-04-15 updated the Arduino sketch directory
2021-04-21 Update README.md
    Added the forum link.
2021-04-28 Fixed loading myIp, outPort and mac when the DIP sw changed.
2021-04-30 Added EL_POS functions
    setElPos() and getElPos.
2021-04-30 reportStall is now disabled as an default condition
2021-05-02 Fixed loading bool values from config.txt
    Now integer values can be used for bool values.
2021-05-03 Updated the Arduino sketch folder
2021-05-09 Fixed some typos in the hardware inspection sketch
2021-06-28 Update the Ponoor PowerSTEP01 Library version number.
2021-09-03 update the getElPos() response and diagnosis outputs
2021-09-08 configTools CSS updated
2021-11-22 added minSpeed functions
2021-11-22 minSpeed OSC commands update
2021-11-24 configTool update and some bugfixes for minSpeed/lowSpeedOptimization
2021-11-24 change double constants to float constants
2021-11-25 Update getLowSpeedOptimizeThreshold return value
2021-11-25 Update /getMinSpeed command
2021-12-02 added /resetDevice and remove resetDev command
2021-12-03 Added updatePositionReport commands
2021-12-03 added /getPositionList
2021-12-04 confifgTool updating (not completed yet)
2021-12-06 config tool reportPositionListInterval
2021-12-07 changed command names /enablePositionReport to /setPositionReportInterval
2021-12-08 Update setElPos arguments and bug fixes for loading config
2021-12-08 updated Arduino sketch folder
2021-12-09 Fixed the response of /getLimitSw
2022-02-13 check the homing status for motion/stop commands
2022-02-14 Arduino sketch folder sync
2022-02-14 only `/run` can interrupt a homing among motion commands.
    Other motion commands will be ignored during a homing.
2022-03-03 Fixed the incorrect `/getHomeSw` response.
2022-03-24 Added the link to the latest firmware repository.
2022-03-28 File name typo fixed step400_r1_schematics.pdf
2024-03-01 Added the LED test for hardware test firmware
    Also convert the Arduino project to the platformIO project
2024-03-03 test firmware update
2024-03-04 Fixed some alarms during the test.
2024-03-06 fixed some bugs
2024-03-07 Remove old firmware directories.
2024-03-07 BOM update for r1.0.1
